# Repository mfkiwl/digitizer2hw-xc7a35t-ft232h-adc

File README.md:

# Digitizer2 TDC hardware
The digitizer2 project is a low-cost, high speed analog-to-digital converter with customizable signal processing logic.

Hardware
---
- Xilinx Artix7 FPGA (XC7A35T)
- 500 MHz, 12bit ADC (ADS5403)
- DDR3 Memory, 128 MB (MT41J128M16)
- USB 2.0, Hi-Speed (FT2232H)

Related repositories
---
- [FPGA device server](https://github.com/pwuertz/fpga-device-server)
- [Digitizer2 Firmware](https://github.com/pwuertz/digitizer2fw)
- [Digitizer2 Hardware](https://github.com/pwuertz/digitizer2hw)

License
---
This project is free software. You can redistribute it and/or modify it under the terms of the [GNU General Public License](COPYING.txt).

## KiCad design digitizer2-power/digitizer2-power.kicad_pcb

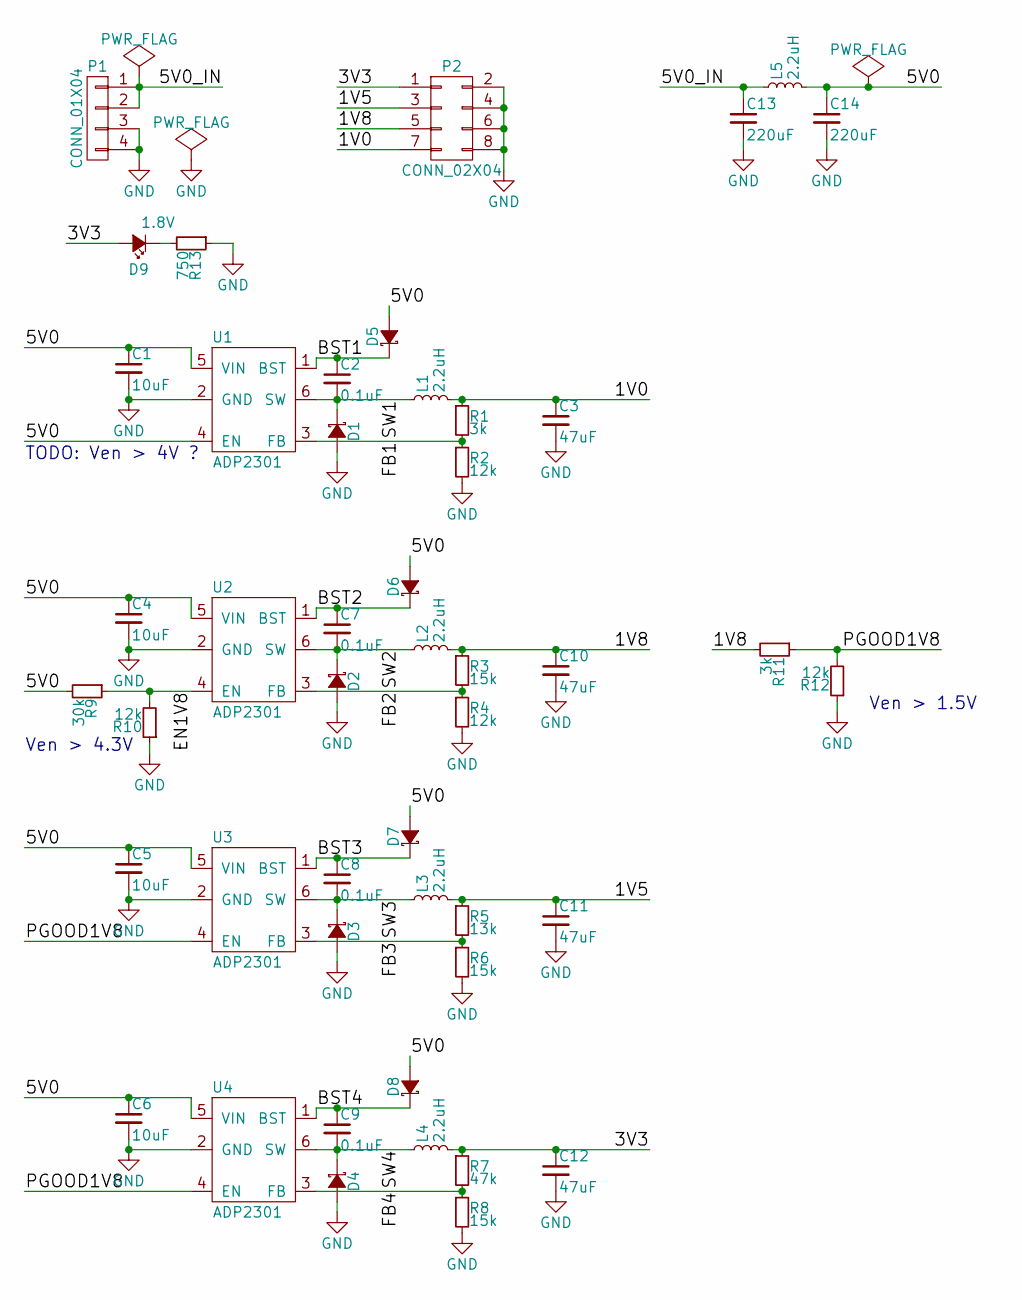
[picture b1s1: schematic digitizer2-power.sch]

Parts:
C1, C4, C5, C6: 10uF; C_1206; MPN GRM32DR61C106KA01L
C2, C7, C8, C9: 0.1uF; C_0603_HandSoldering; MPN GRM188R72A104KA35D
C3, C10, C11, C12: 47uF; C_1210; MPN GRM32ER61A476KE20L
C13, C14: 220uF; c_elec_5x5.7; MPN 6SVPE220MW
D1, D2, D3, D4: D_Schottky_Small; SMA_Standard; MPN B230A-13-F
D5, D6, D7, D8: D_Schottky_Small; SOD-123; MPN BAT42W
D9: 1.8V; LED_0603
L1, L2, L3, L4, L5: 2.2uH; IHLP-1212BZ-11; MPN IHLP1212BZER2R2M11
P1: CONN_01X04; Pin_Header_Straight_1x04
P2: CONN_02X04; Pin_Header_Straight_2x04
R1, R11: 3k; R_0603_HandSoldering
R2, R4, R10, R12: 12k; R_0603_HandSoldering
R3, R6, R8: 15k; R_0603_HandSoldering
R5: 13k; R_0603_HandSoldering
R7: 47k; R_0603_HandSoldering
R9: 30k; R_0603_HandSoldering
R13: 750; R_0603_HandSoldering
U1, U2, U3, U4: ADP2301; SOT-23-6; MPN ADP2301AUJZ-R7

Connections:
/1V0: C3.1, L1.2, P2.7, R1.1
/1V5: C11.1, L3.2, P2.3, R5.1
/1V8: C10.1, L2.2, P2.5, R3.1, R11.2
/3V3: C12.1, D9.2 (A), L4.2, P2.1, R7.1
/5V0: C1.1, C4.1, C5.1, C6.1, C14.1, D5.2 (A), D6.2 (A), D7.2 (A), D8.2 (A), L5.2, R9.2, U1.4 (EN), U1.5 (VIN), U2.5 (VIN), U3.5 (VIN), U4.5 (VIN)
/5V0_IN: C13.1, L5.1, P1.1, P1.2
/BST1: C2.1, D5.1 (K), U1.1 (BST)
/BST2: C7.1, D6.1 (K), U2.1 (BST)
/BST3: C8.1, D7.1 (K), U3.1 (BST)
/BST4: C9.1, D8.1 (K), U4.1 (BST)
/EN1V8: R9.1, R10.2, U2.4 (EN)
/FB1: R1.2, R2.1, U1.3 (FB)
/FB2: R3.2, R4.1, U2.3 (FB)
/FB3: R5.2, R6.1, U3.3 (FB)
/FB4: R7.2, R8.1, U4.3 (FB)
/PGOOD1V8: R11.1, R12.2, U3.4 (EN), U4.4 (EN)
/SW1: C2.2, D1.1 (K), L1.1, U1.6 (SW)
/SW2: C7.2, D2.1 (K), L2.1, U2.6 (SW)
/SW3: C8.2, D3.1 (K), L3.1, U3.6 (SW)
/SW4: C9.2, D4.1 (K), L4.1, U4.6 (SW)
GND: C1.2, C3.2, C4.2, C5.2, C6.2, C10.2, C11.2, C12.2, C13.2, C14.2, D1.2 (A), D2.2 (A), D3.2 (A), D4.2 (A), P1.3, P1.4, P2.2, P2.4, P2.6, P2.8, R2.2, R4.2, R6.2, R8.2, R10.1, R12.1, R13.1, U1.2 (GND), U2.2 (GND), U3.2 (GND), U4.2 (GND)
unnamed: D9.1 (K), R13.2

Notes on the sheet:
TODO: Ven > 4V ?
Ven > 4.3V
Ven > 1.5V

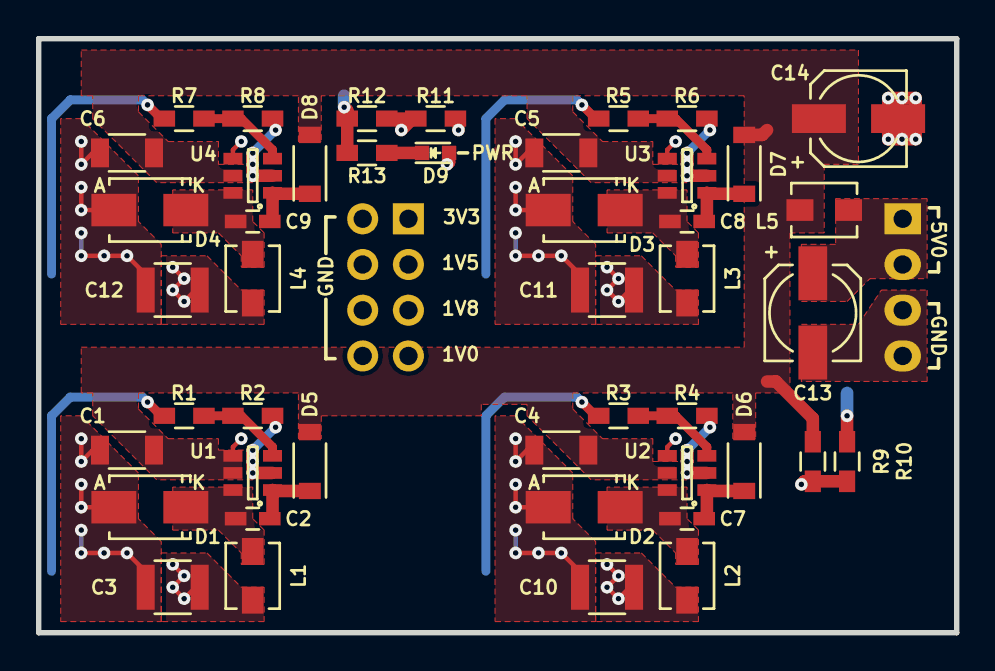
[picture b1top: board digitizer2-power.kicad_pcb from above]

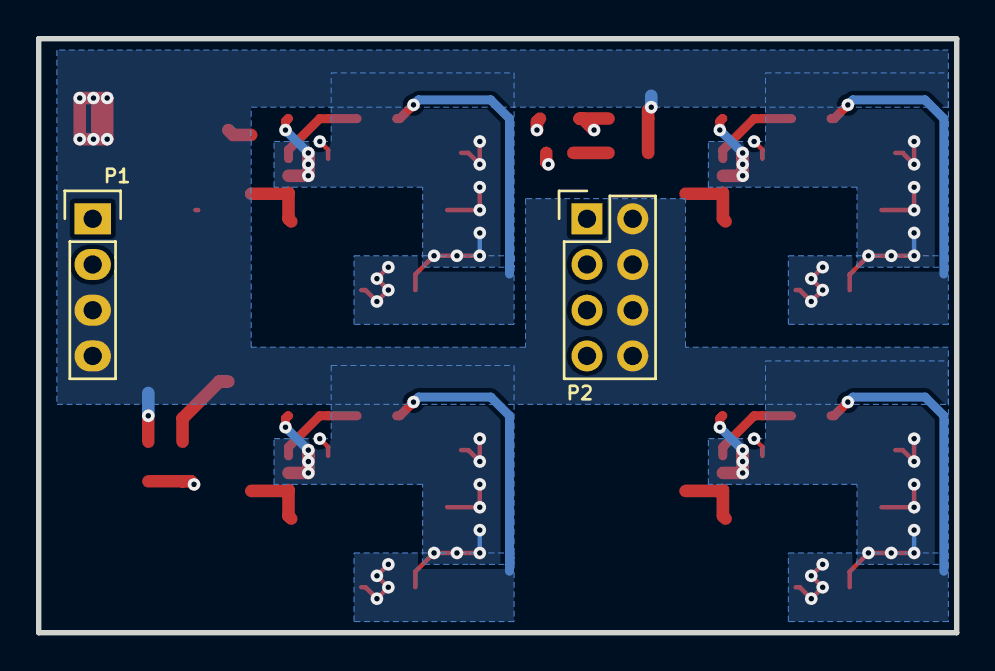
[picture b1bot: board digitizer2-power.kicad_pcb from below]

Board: 4 copper layers, 51.0 x 33.0 mm, 47 parts (2 on the bottom side), 22 nets.

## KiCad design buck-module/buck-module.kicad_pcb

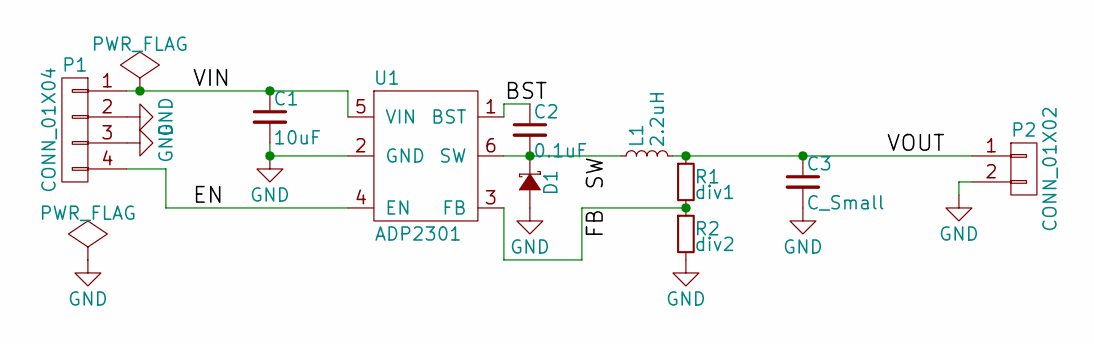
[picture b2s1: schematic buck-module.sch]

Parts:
C1: 10uF; C_1206; MPN GRM32DR61C106KA01L
C2: 0.1uF; C_0603_HandSoldering
C3: C_Small; C_1210; MPN GRM32ER61A476KE20L
D1: D_Schottky_Small; SMA_Standard; MPN B230A-13-F
L1: 2.2uH; IHLP-1212BZ-11; MPN IHLP1212BZER2R2M11
P1: CONN_01X04; Pin_Header_Straight_1x04
P2: CONN_01X02; Pin_Header_Straight_1x02
R1: div1; R_0603_HandSoldering
R2: div2; R_0603_HandSoldering
U1: ADP2301; SOT-23-6; MPN ADP2301AUJZ-R7

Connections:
/BST: C2.1, U1.1 (BST)
/EN: P1.4, U1.4 (EN)
/FB: R1.2, R2.1, U1.3 (FB)
/SW: C2.2, D1.1 (K), L1.1, U1.6 (SW)
/VIN: C1.1, P1.1, U1.5 (VIN)
/VOUT: C3.1, L1.2, P2.1, R1.1
GND: C1.2, C3.2, D1.2 (A), P1.2, P1.3, P2.2, R2.2, U1.2 (GND)

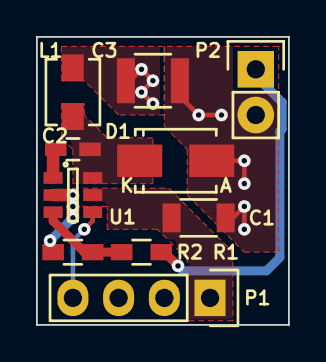
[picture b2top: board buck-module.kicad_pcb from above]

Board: 2 copper layers, 14.0 x 16.0 mm, 10 parts (0 on the bottom side), 7 nets.
